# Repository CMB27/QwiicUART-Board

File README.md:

# QwiicUART Board

Have you ever needed another Serial (UART) port, but your microcontroller doesn't have any more.
This board allows you to add up to four Serial ports via the Qwiic system.

This is a breakout board for the NXP SC16IS741A.
The SC16IS741A is a UART controlled using an I<sup>2</sup>C or SPI interface.
This board is only setup to be able to utilize the I<sup>2</sup>C interface.

> [!NOTE]
> This design is distributed WITHOUT ANY EXPRESS OR IMPLIED WARRANTY, INCLUDING OF MERCHANTABILITY, SATISFACTORY QUALITY AND FITNESS FOR A PARTICULAR PURPOSE.

> [!WARNING]
> Applying voltages higher than 3.3V to any I/O pin could damage the board.

### Documentation
- [Schematic](QwiicUART-Board.pdf)
- [KiCad Source Files](src)
- [QwiicUART Library](https://github.com/CMB27/QwiicUART-Library)
- [SparkFun Qwiic Landing Page](https://www.sparkfun.com/qwiic)
- [NXP SC16IS741A Datasheet](https://www.nxp.com/docs/en/data-sheet/SC16IS741A.pdf)

## Components

### Circuit Board Specifications
- Board Length: **25.4 mm**
- Board Width: **25.4 mm**
- Board Thickness: **1.6 mm**
- Substrate Material: **FR4**
- Copper Layers: **2**
- Copper Thickness: **1 oz**
- Soldermask Color: **Any** (Blue Suggested)
- Surface Finish: **Any** (HASL Lead-Free Suggested)
- Smallest Hole Diameter: **0.3 mm [11.8 mil]**
- Smallest Trace Width: **0.2 mm [7.8 mil]**
- Smallest Trace Spacing: **0.2 mm [7.8 mil]**

### Purchase Components
| References | Quantity | Manufacturer | Part Number            | Description           |
| :--------- | :------: | :----------- | :--------------------- | :-------------------- |
| C1, C2     |        2 | Samsung      | CL10B104KB8NNWC        | 0.1uF 0603 Capacitor  |
| J1, J2     |        2 | JST          | SM04B-SRSS-TB(LF)(SN)  | 4-Position Connector  |
| R1, R2     |        2 | YAGEO        | RC0603JR-071KL         | 1K Ohm 0603 Resistor  |
| U1         |        1 | NXP          | SC16IS741AIPWJ         | UART IC               |
| X1         |        1 | ECS          | ECS-2520MVLC-018-BN-TR | 1.8432 HMz Oscillator |

## Assembly

All components are assembled to the top side of the board.
See the image above for component locations.

On the back side of the board there are several solder jumper locations.
By default the lower `0x48` jumper is connected.
This connection can be cut and another jumper can be soldered to change the I<sup>2</sup>C address.

> [!WARNING]
> Powering up the board with more than one jumper soldered/connected could result in a short ciruit damaging the board.

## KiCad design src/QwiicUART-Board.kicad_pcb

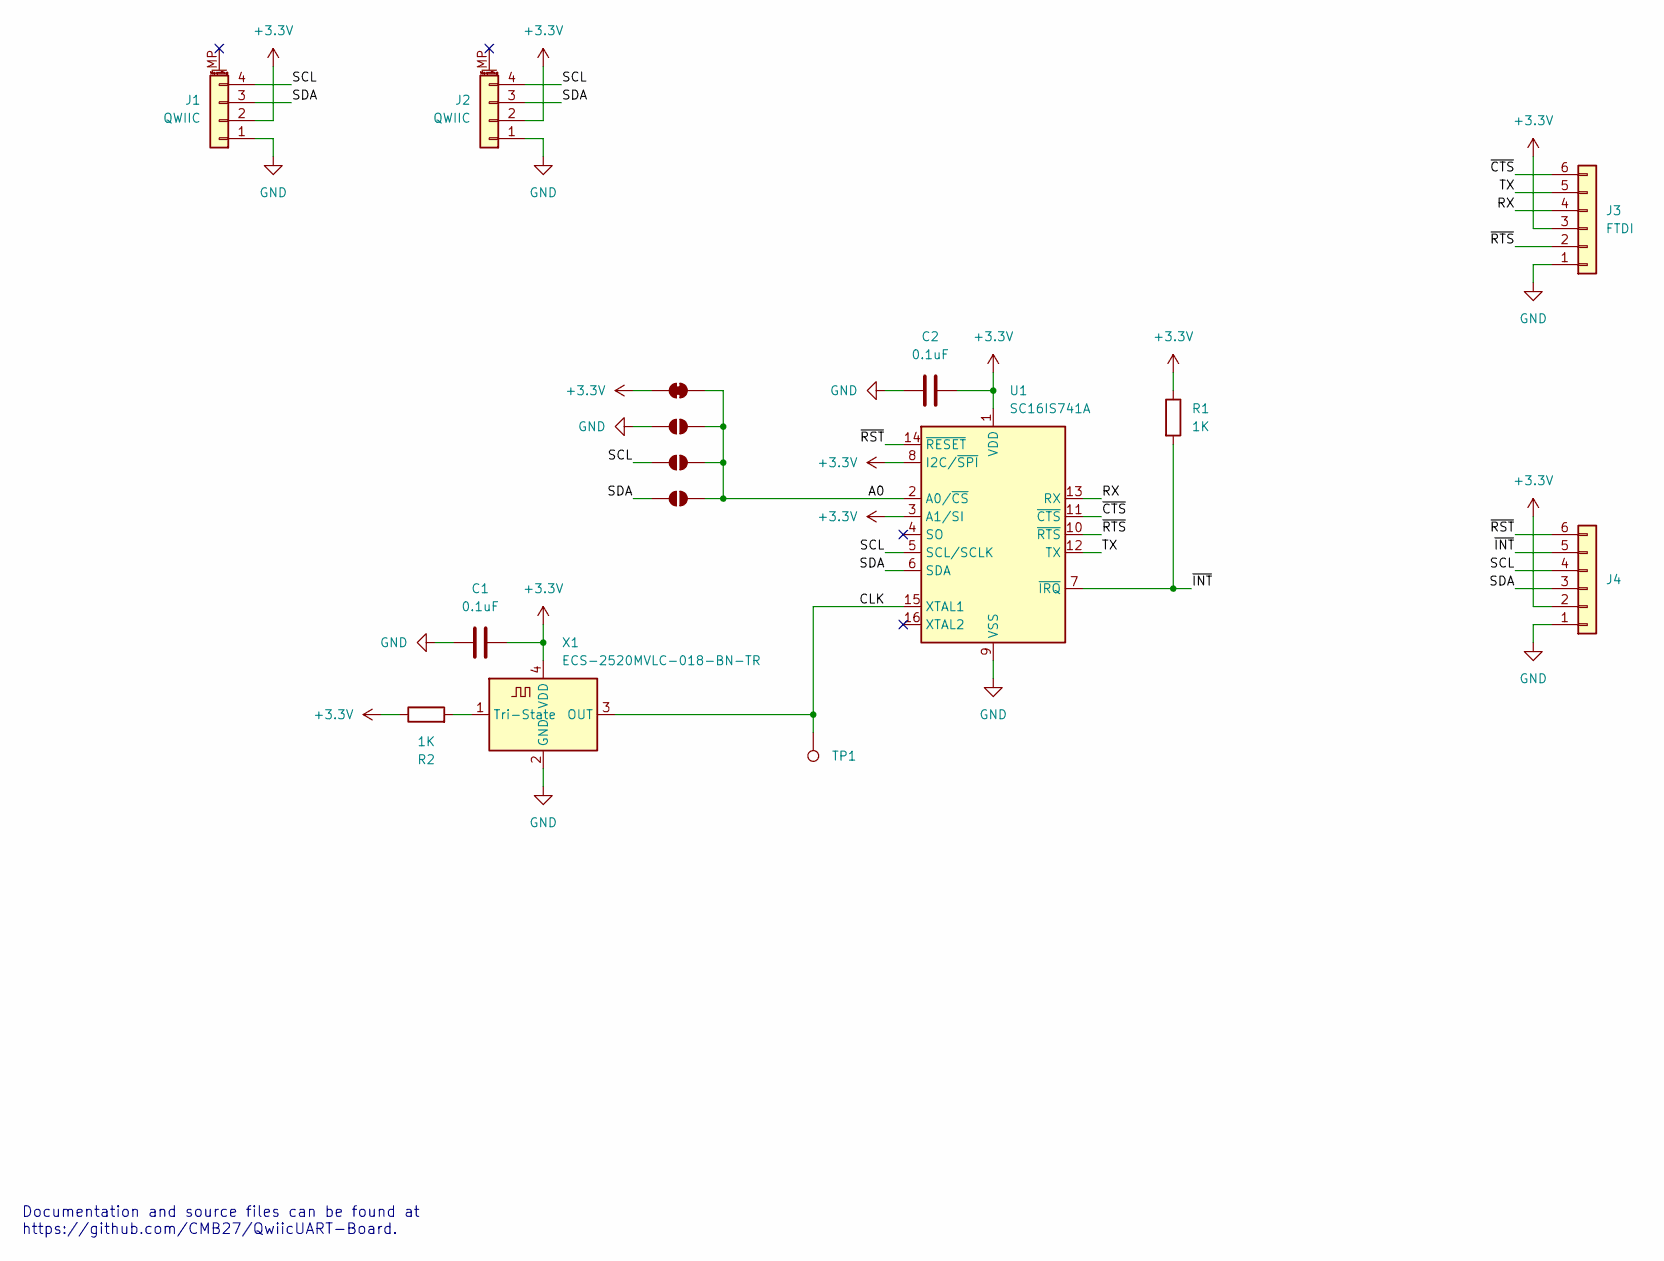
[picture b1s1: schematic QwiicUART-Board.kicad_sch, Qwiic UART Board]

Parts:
C1, C2: 0.1uF; C_0603_1608Metric_Pad1.08x0.95mm_HandSolder
J1, J2: QWIIC; JST_SH_SM04B-SRSS-TB_1x04-1MP_P1.00mm_Horizontal
J3: FTDI; PinHeader_1x06_P2.54mm
J4: PinHeader_1x06_P2.54mm
JP1: SolderJumper_2_Bridged; SolderJumper-2_P1.3mm_Bridged_RoundedPad1.0x1.5mm
JP2, JP3, JP4: SolderJumper_2_Open; SolderJumper-2_P1.3mm_Open_RoundedPad1.0x1.5mm
R1, R2: 1K; R_0603_1608Metric_Pad0.98x0.95mm_HandSolder
TP1: TestPoint; TestPoint_THTPad_D1.0mm_Drill0.5mm
U1: SC16IS741A; TSSOP-16_4.4x5mm_P0.65mm
X1: ECS-2520MVLC-018-BN-TR; Oscillator_SMD_ECS_2520MV-xxx-xx-4Pin_2.5x2.0mm

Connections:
+3.3V: C1.2, C2.2, J1.2, J2.2, J3.3, J4.2, JP1.1 (A), R1.1, R2.1, U1.1 (VDD), U1.3 (A1/SI), U1.8 (I2C/~SPI), X1.4 (VDD)
/A0: JP1.2 (B), JP2.2 (B), JP3.2 (B), JP4.2 (B), U1.2 (A0/~CS)
/CLK: TP1.1, U1.15 (XTAL1), X1.3 (OUT)
/RX: J3.4, U1.13 (RX)
/SCL: J1.4, J2.4, J4.4, JP3.1 (A), U1.5 (SCL/SCLK)
/SDA: J1.3, J2.3, J4.3, JP4.1 (A), U1.6 (SDA)
/TX: J3.5, U1.12 (TX)
/~CTS: J3.6, U1.11 (~CTS)
/~INT: J4.5, R1.2, U1.7 (~IRQ)
/~RST: J4.6, U1.14 (~RESET)
/~RTS: J3.2, U1.10 (~RTS)
GND: C1.1, C2.1, J1.1, J2.1, J3.1, J4.1, JP2.1 (A), U1.9 (VSS), X1.2 (GND)
unnamed: R2.2, X1.1 (Tri-State)

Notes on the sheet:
Documentation and source files can be found at https://github.com/CMB27/QwiicUART-Board.

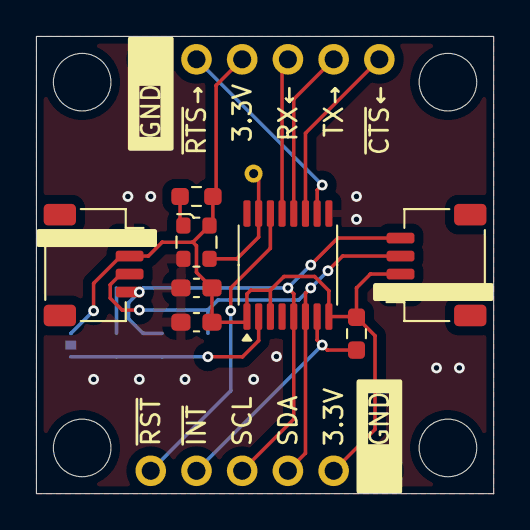
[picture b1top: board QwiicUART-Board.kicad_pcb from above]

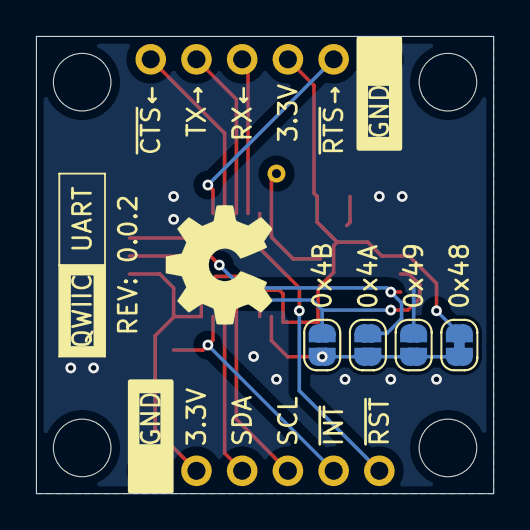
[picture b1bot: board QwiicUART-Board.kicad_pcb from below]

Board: 2 copper layers, 25.4 x 25.4 mm, 15 parts (4 on the bottom side), 13 nets.

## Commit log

2025-01-11 Made some refinements
2025-01-11 Finished board design
2025-01-12 Added/generated essential files
2025-02-09 Changed repository name. Changed address numbers on back of board. Added a test point for the clock.

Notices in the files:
src/QwiicUART-Board.kicad_pcb:
© 2025 C. M. Bulliner. Released under the CERN-OHL-P v2 license.
